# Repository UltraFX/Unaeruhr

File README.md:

# Unaeruhr
Code and Layout for my unary clock

The unary clock is inspired by the clock on the "Rheinturm" in Düsseldorf, Germany. 

It's three lines with each tens (10-50) and ones (1-9) to display hours, minutes and seconds.
With a button, the display can be switched to show the date (month and day).
Another button can control the time

Later, DCF77 will be added to update the time automatically.

Still Work in Progress!!

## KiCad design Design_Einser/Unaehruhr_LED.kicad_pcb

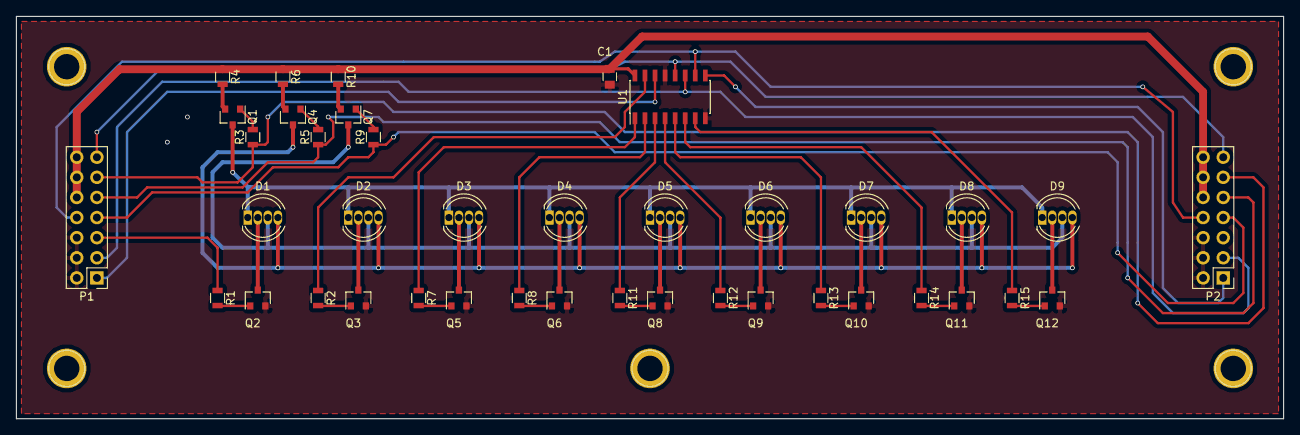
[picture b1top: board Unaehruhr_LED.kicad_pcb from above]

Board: 2 copper layers, 160.0 x 50.8 mm, 40 parts (0 on the bottom side), 46 nets.

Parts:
C1: 100n; C_0805
D1, D2, D3, D4, D5, D6, D7, D8, D9: LED_RCBG; LED_D5.0mm-4
P1: INPUT; Pin_Header_Straight_2x07_Pitch2.54mm
P2: OUTPUT; Pin_Header_Straight_2x07_Pitch2.54mm
Q1, Q4, Q7: Q_PNP_BEC; SOT-23
Q2, Q3, Q5, Q6, Q8, Q9, Q10, Q11, Q12: BC849; SOT-23
R1, R2, R3, R5, R7, R8, R9, R11, R12, R13, R14, R15: 10k; R_0805
R4, R6, R10: 68; R_0805
U1: 74HC595; SOIC-16_3.9x9.9mm_Pitch1.27mm

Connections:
+5V: C1.1, P1.10, P1.12, P1.14, P2.10, P2.12, P2.14, R4.1, R6.1, R10.1, U1.16
B: P1.7, P2.7, R9.1
D_OUT: P2.1, U1.9
G: P1.9, P2.9, R5.1
GND: C1.2, P1.2, P1.4, P1.6, P2.2, P2.4, P2.6, Q2.2, Q3.2, Q5.2, Q6.2, Q8.2, Q9.2, Q10.2, Q11.2, Q12.2, U1.8, U1.13
LATCH: P1.13, P2.13, U1.12
LED0: P1.5, R1.1
LED1: R2.1, U1.15
LED2: R7.1, U1.1
LED3: R8.1, U1.2
LED4: R11.1, U1.3
LED5: R12.1, U1.4
LED6: R13.1, U1.5
LED7: R14.1, U1.6
LED8: R15.1, U1.7
MOSI: P1.1, U1.14
unnamed: D1.1, D2.1, D3.1, D4.1, D5.1, D6.1, D7.1, D8.1, D9.1, Q1.3
unnamed: D1.2, Q2.3
unnamed: D1.3, D2.3, D3.3, D4.3, D5.3, D6.3, D7.3, D8.3, D9.3, Q7.3
unnamed: D1.4, D2.4, D3.4, D4.4, D5.4, D6.4, D7.4, D8.4, D9.4, Q4.3
unnamed: D2.2, Q3.3
unnamed: D3.2, Q5.3
unnamed: D4.2, Q6.3
unnamed: D5.2, Q8.3
unnamed: D6.2, Q9.3
unnamed: D7.2, Q10.3
unnamed: D8.2, Q11.3
unnamed: D9.2, Q12.3
unnamed: Q1.1, R3.2
unnamed: Q1.2, R4.2
unnamed: Q2.1, R1.2
unnamed: Q3.1, R2.2
unnamed: Q4.1, R5.2
unnamed: Q4.2, R6.2
unnamed: Q5.1, R7.2
unnamed: Q6.1, R8.2
unnamed: Q7.1, R9.2
unnamed: Q7.2, R10.2
unnamed: Q8.1, R11.2
unnamed: Q9.1, R12.2
unnamed: Q10.1, R13.2
unnamed: Q11.1, R14.2
unnamed: Q12.1, R15.2
R: P1.11, P2.11, R3.1
RES: P1.8, P2.8, U1.10
SCK: P1.3, P2.3, U1.11

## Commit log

2017-07-25 :neckbeard: Added .gitattributes & .gitignore files
2017-07-25 Folder and File structure
    Added files
2017-07-25 Created Readme
2017-07-27 Added Off-On-Automatism
    Not working yet
2017-07-28 Created MIT License
    License for this project
2017-08-03 Bugfixes for Time-Setup
    Changelog:
    - Date/Time Setup working
    - On-/Off-Time Setup working
    - Blackout working
    Bugs:
    - Seconds not counting properly
2017-09-24 experiments
    Just tried out some stuff. Clock not working properly in this state
2017-09-24 nothing special
2017-09-28 Fixes
    Still searching for the problem.. harddrive crashed
2017-10-05 Revert "Fixes"
    This reverts commit c3892c757fe040b767fd768806e603a6775c86c4.
2017-10-05 Fixed some bugs
    Clock and On-Off-Time working so far. Still have the issue that seconds overjump...
